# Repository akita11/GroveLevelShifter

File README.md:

# GroveLevelShifter

2本のGroveケーブルを接続して延長し、その中の電源電圧(+5V)を3.3Vに変換します。M5StackシリーズのGrove互換コネクタ（HY4pコネクタ）は電源電圧が5Vですが、信号電圧は3.3Vのため、信号電圧レベルをあわせるのに利用できます。その他のGNDと2本の信号線はそのまま接続されています。

## 使い方

2つのGroveコネクタのうち、"5V"と書いてある側（"GroveLevelShifetr"の文字がある側）に、電源供給側（M5Stackなど）からのGroveケーブルを接続します。反対側の"3.3V"と書いてある側（IC等の部品が乗っている側）のGroveコネクタの電源には3.3Vが出力されますので、Groveケーブルで3.3Vを供給したいセンサ等に接続します。

## Author

Junichi Akita (akita@ifdl.jp, @akita11)

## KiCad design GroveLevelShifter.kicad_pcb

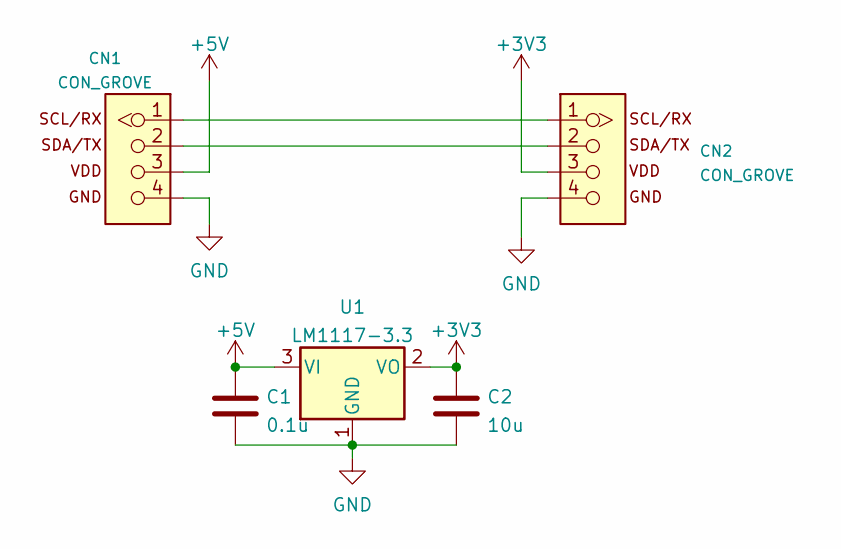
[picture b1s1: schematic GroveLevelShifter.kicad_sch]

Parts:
C1: 0.1u; C_0603_1608Metric
C2: 10u; C_0603_1608Metric
CN1, CN2: CON_GROVE; CON_GROVE_H
U1: LM1117-3.3; SOT-223-3_TabPin2

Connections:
+3V3: C2.1, CN2.3, U1.2 (VO)
+5V: C1.1, CN1.3, U1.3 (VI)
GND: C1.2, C2.2, CN1.4, CN2.4, U1.1 (GND)
unnamed: CN1.1, CN2.1
unnamed: CN1.2, CN2.2

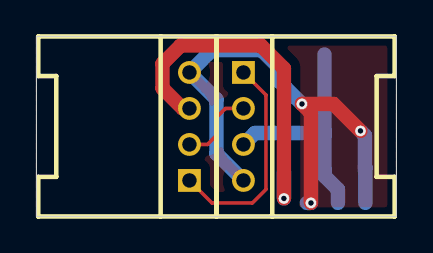
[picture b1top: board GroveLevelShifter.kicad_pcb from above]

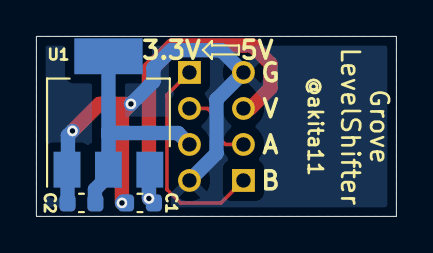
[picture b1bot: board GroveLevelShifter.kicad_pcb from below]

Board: 2 copper layers, 20.0 x 10.0 mm, 5 parts (3 on the bottom side), 5 nets.

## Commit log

2023-12-24 update photo
